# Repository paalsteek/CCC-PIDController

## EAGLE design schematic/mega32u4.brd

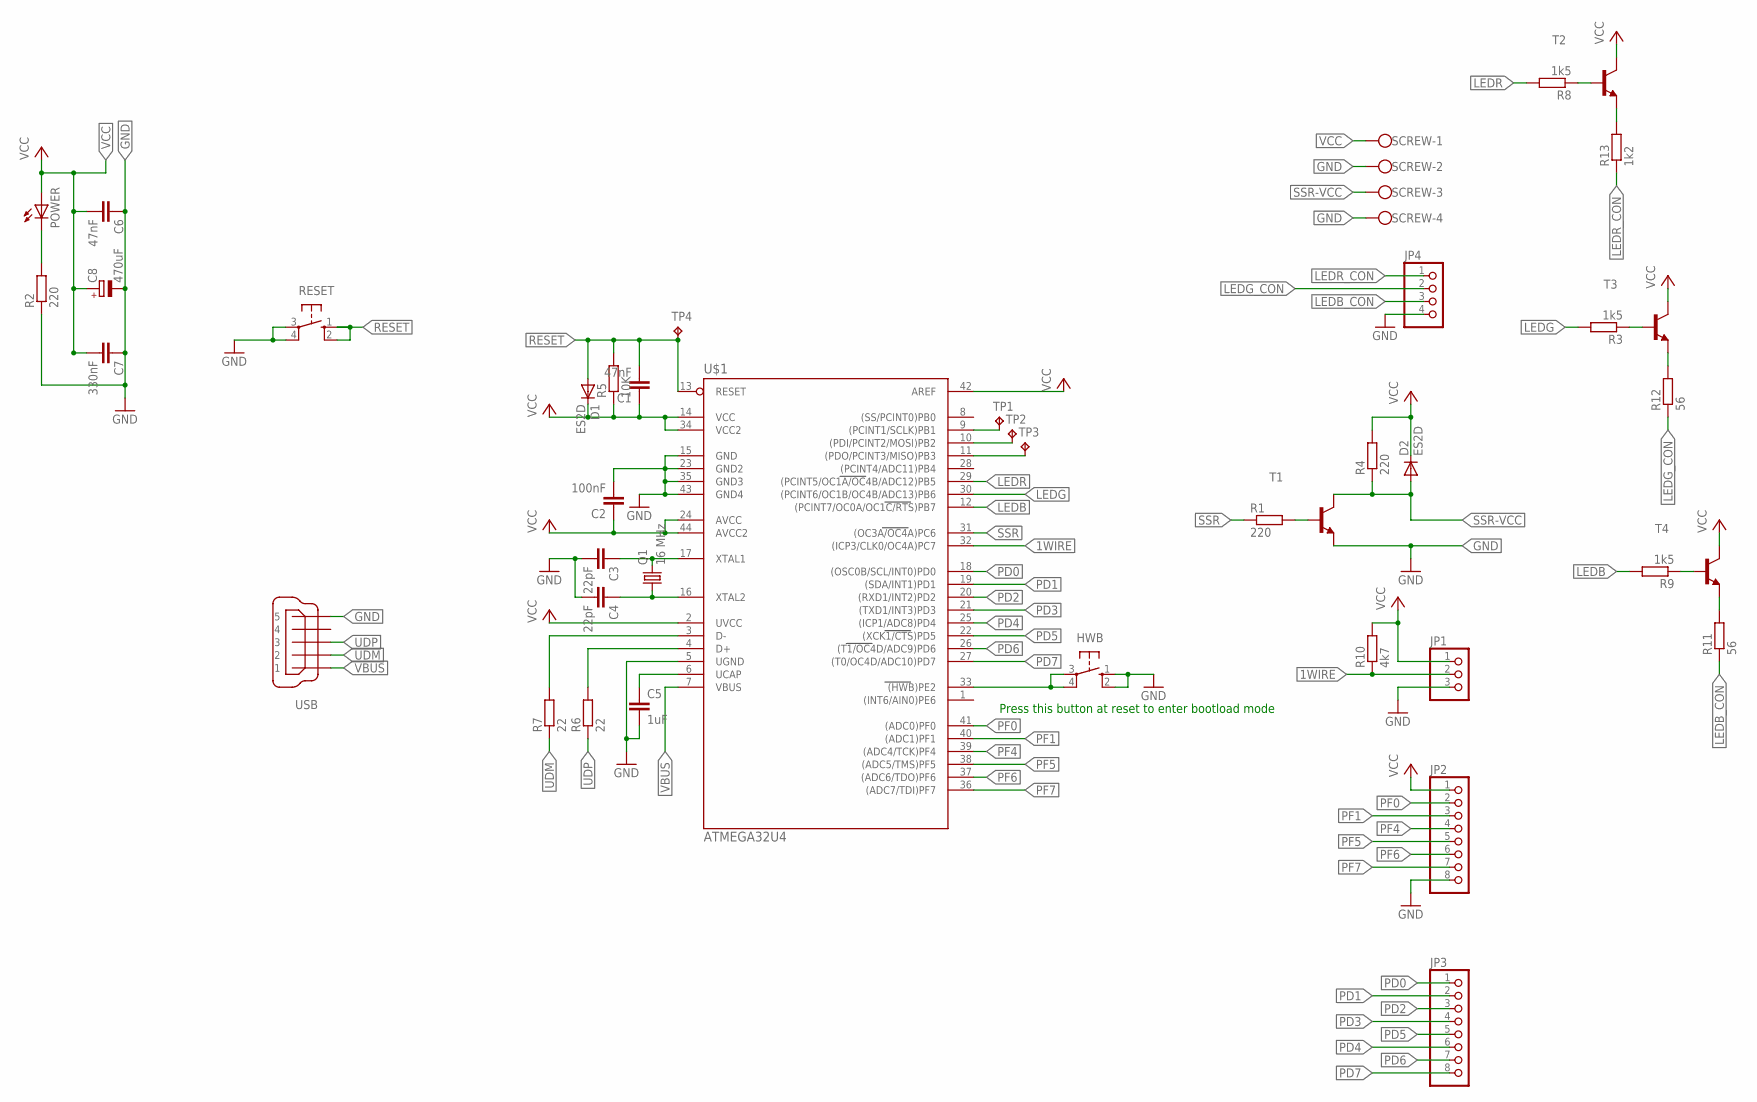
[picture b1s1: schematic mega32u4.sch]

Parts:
C1, C6: 47nF; C0805K
C2: 100nF; C0805K
C3, C4: 22pF; C0805K
C5: 1uF; C0805K
C7: 330nF; C0805K
C8: 470uF; 150CLZ-0810
D1, D2: ES2D; SMB
HWB: 10-XX; B3F-10XX
JP1: PINHD-1X3; 1X03
JP2, JP3: PINHD-1X8; 1X08
JP4: PINHD-1X4; 1X04
POWER: LEDSML0805; SML0805
Q1: 16 MHz; CTS406
R1, R2, R4: 220; R0805
R3, R8, R9: 1k5; R0805
R5: 10K; R0805
R6, R7: 22; R0805
R10: 4k7; R0805
R11, R12: 56; R0805
R13: 1k2; R0805
RESET: 10-XX; B3F-10XX; MPN B3F-1000
SCREW: W237-4
T1, T2, T3, T4: BC817-25-NPN-SOT23-BEC; SOT23-BEC
TP1, TP2, TP3, TP4: TPTP10R; TP10R
U$1: ATMEGA32U4; TQFP44
USB: MINI-USB-32005-201; 32005-201

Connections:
1WIRE: JP1.2, R10.1, U$1.32 ((ICP3/CLK0/OC4A)PC7)
GND: C2.2, C3.2, C4.2, C5.2, C6.1, C7.1, C8.-, HWB.1 (S), HWB.2 (S1), JP1.3, JP2.8, JP4.4, R2.1, RESET.3, RESET.4 (P1), SCREW.2, SCREW.4, T1.E, U$1.5 (UGND), U$1.15 (GND), U$1.23 (GND2), U$1.35 (GND3), U$1.43 (GND4), USB.5
LEDB: R9.2, U$1.12 ((PCINT7/OC0A/OC1C/RTS)PB7)
LEDB_CON: JP4.3, R11.1
LEDG: R3.2, U$1.30 ((PCINT6/OC1B/OC4B/ADC13)PB6)
LEDG_CON: JP4.2, R12.1
LEDR: R8.2, U$1.29 ((PCINT5/OC1A/OC4B/ADC12)PB5)
LEDR_CON: JP4.1, R13.1
unnamed: TP1.TP, U$1.9 ((PCINT1/SCLK)PB1)
unnamed: C3.1, Q1.3 (2), U$1.17 (XTAL1)
unnamed: C4.1, Q1.1, U$1.16 (XTAL2)
unnamed: C5.1, U$1.6 (UCAP)
unnamed: R1.2, T1.B
unnamed: R6.2, U$1.4 (D+)
unnamed: R7.2, U$1.3 (D-)
unnamed: R8.1, T2.B
unnamed: R3.1, T3.B
unnamed: HWB.3, HWB.4 (P1), U$1.33 ((HWB)PE2)
unnamed: R9.1, T4.B
unnamed: TP2.TP, U$1.10 ((PDI/PCINT2/MOSI)PB2)
unnamed: POWER.C, R2.2
unnamed: R11.2, T4.E
unnamed: R12.2, T3.E
unnamed: R13.2, T2.E
unnamed: TP3.TP, U$1.11 ((PDO/PCINT3/MISO)PB3)
PD0: JP3.1, U$1.18 ((OSC0B/SCL/INT0)PD0)
PD1: JP3.2, U$1.19 ((SDA/INT1)PD1)
PD2: JP3.3, U$1.20 ((RXD1/INT2)PD2)
PD3: JP3.4, U$1.21 ((TXD1/INT3)PD3)
PD4: JP3.6, U$1.25 ((ICP1/ADC8)PD4)
PD5: JP3.5, U$1.22 ((XCK1/CTS)PD5)
PD6: JP3.7, U$1.26 ((T1/OC4D/ADC9)PD6)
PD7: JP3.8, U$1.27 ((T0/OC4D/ADC10)PD7)
PF0: JP2.2, U$1.41 ((ADC0)PF0)
PF1: JP2.3, U$1.40 ((ADC1)PF1)
PF4: JP2.4, U$1.39 ((ADC4/TCK)PF4)
PF5: JP2.5, U$1.38 ((ADC5/TMS)PF5)
PF6: JP2.6, U$1.37 ((ADC6/TDO)PF6)
PF7: JP2.7, U$1.36 ((ADC7/TDI)PF7)
RESET: C1.2, D1.A, R5.2, RESET.1 (S), RESET.2 (S1), TP4.TP, U$1.13 (RESET)
SSR: R1.1, U$1.31 ((OC3A/OC4A)PC6)
SSR-VCC: D2.A, R4.1, SCREW.3, T1.C
UDM: R7.1, USB.2
UDP: R6.1, USB.3
VBUS: U$1.7 (VBUS), USB.1
VCC: C1.1, C2.1, C6.2, C7.2, C8.+, D1.C, D2.C, JP1.1, JP2.1, POWER.A, R4.2, R5.1, R10.2, SCREW.1, T2.C, T3.C, T4.C, U$1.2 (UVCC), U$1.14 (VCC), U$1.24 (AVCC), U$1.34 (VCC2), U$1.42 (AREF), U$1.44 (AVCC2)

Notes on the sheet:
Press this button at reset to enter bootload mode

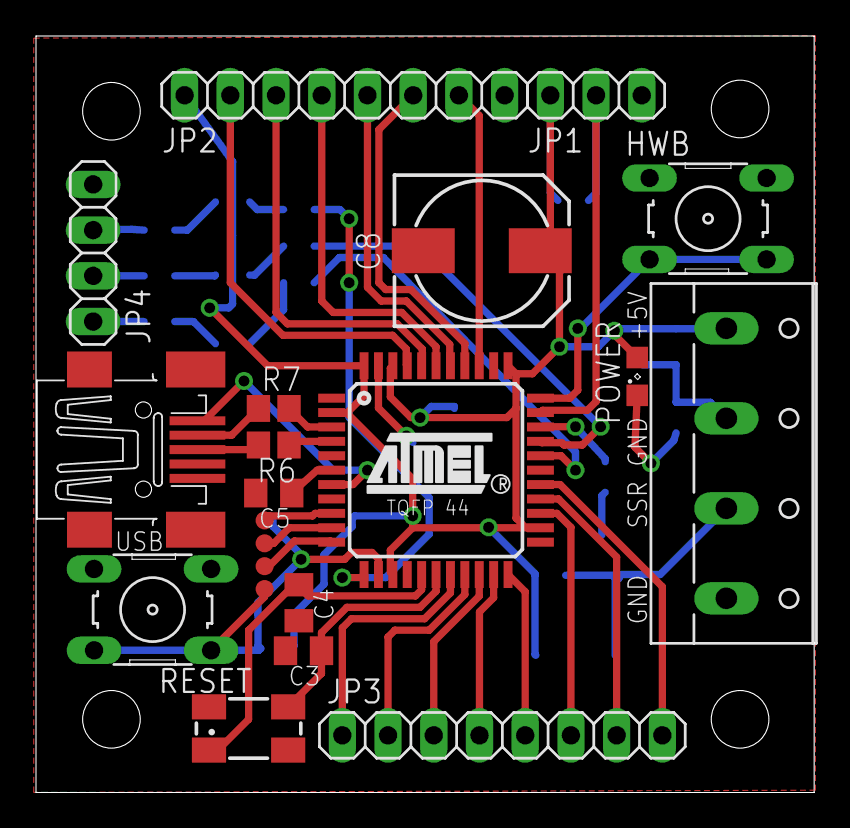
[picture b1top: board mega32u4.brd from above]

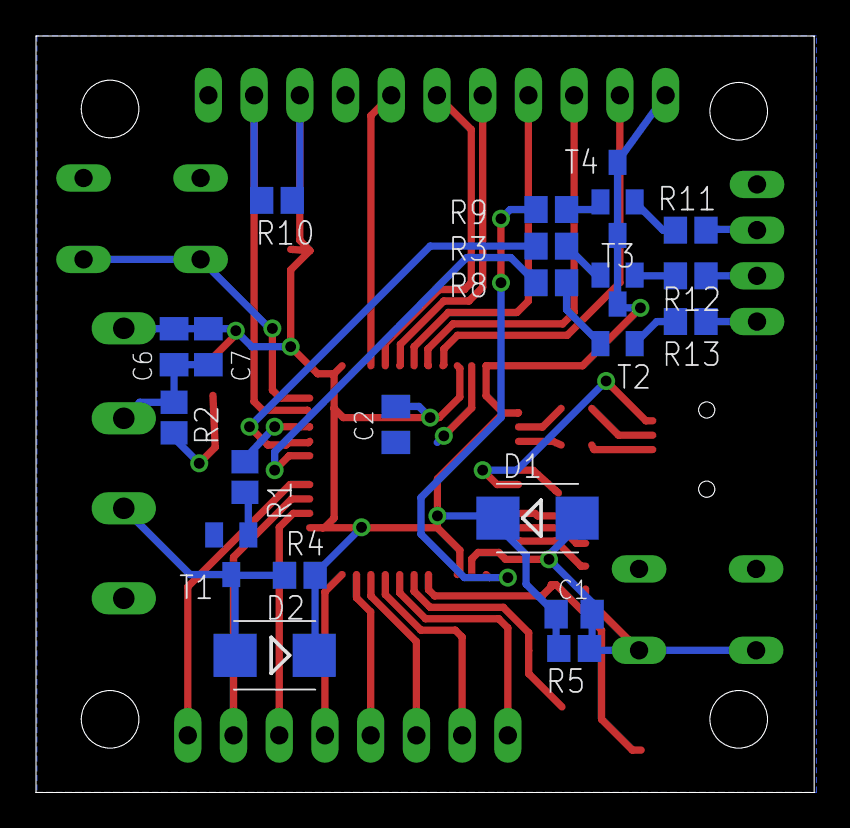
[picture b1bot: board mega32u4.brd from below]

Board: 2 copper layers, 43.2 x 42.0 mm, 42 parts (21 on the bottom side), 46 nets.

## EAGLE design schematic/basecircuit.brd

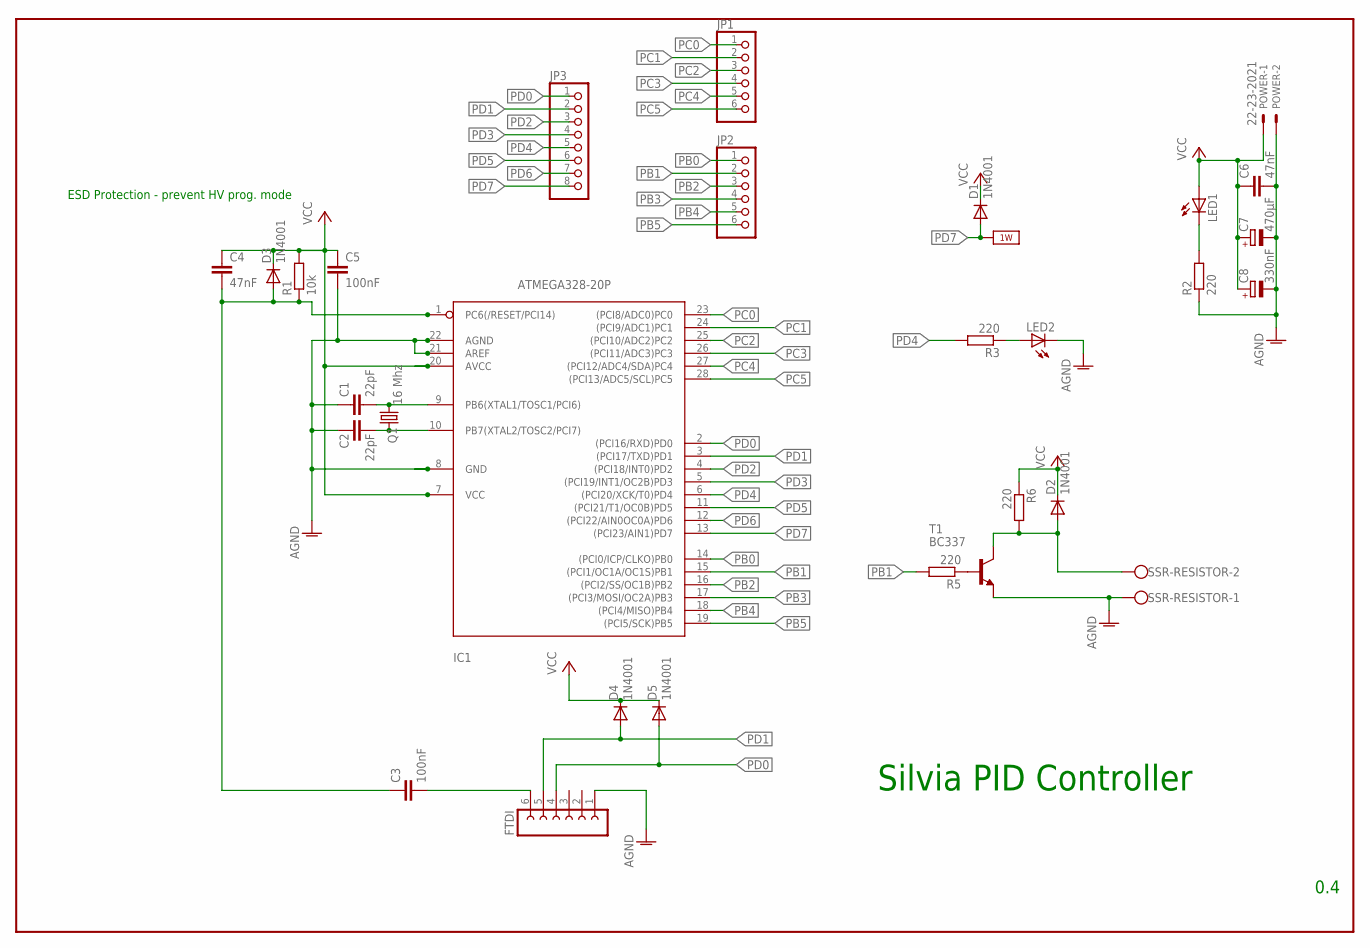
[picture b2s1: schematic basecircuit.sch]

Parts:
C1, C2: 22pF; C025-030X050
C3: 100nF; C025-030X050
C4, C6: 47nF; C025-030X050
C5: 100nF; C025-025X050
C7: 470µF; E2,5-6E
C8: 330nF; E2,5-6E
D1, D2, D3, D4, D5: 1N4001; DO41-10
FTDI: FE06-1; FE06
IC1: ATMEGA328-20P; DIL28-3
JP1, JP2: PINHD-1X6; 1X06
JP3: PINHD-1X8; 1X08
LED1, LED2: LED5MM
POWER: 22-23-2021
Q1: 16 Mhz; HC49U-V
R1: 10k; 0204/7
R2, R3, R5, R6: 220; 0204/7
SSR-RESISTOR: W237-102
T1: BC337; TO92

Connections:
AGND: C1.1, C2.1, C5.2, C6.2, C7.-, C8.-, FTDI.1, IC1.8 (GND), IC1.21 (AREF), IC1.22 (AGND), LED2.K (C), POWER.2, R2.1, SSR-RESISTOR.1, T1.1 (E)
unnamed: R5.1, T1.2 (B)
unnamed: LED1.K (C), R2.2
unnamed: C3.2, FTDI.6
unnamed: LED2.A, R3.1
unnamed: C1.2, IC1.9 (PB6(XTAL1/TOSC1/PCI6)), Q1.2
unnamed: C2.2, IC1.10 (PB7(XTAL2/TOSC2/PCI7)), Q1.1
unnamed: C3.1, C4.2, D3.A, IC1.1 (PC6(/RESET/PCI14)), R1.1
unnamed: D2.A, R6.2, SSR-RESISTOR.2, T1.3 (C)
PB0: IC1.14 ((PCI0/ICP/CLKO)PB0), JP2.1
PB1: IC1.15 ((PCI1/OC1A/OC1S)PB1), JP2.2, R5.2
PB2: IC1.16 ((PCI2/SS/OC1B)PB2), JP2.3
PB3: IC1.17 ((PCI3/MOSI/OC2A)PB3), JP2.4
PB4: IC1.18 ((PCI4/MISO)PB4), JP2.5
PB5: IC1.19 ((PCI5/SCK)PB5), JP2.6
PC0: IC1.23 ((PCI8/ADC0)PC0), JP1.1
PC1: IC1.24 ((PCI9/ADC1)PC1), JP1.2
PC2: IC1.25 ((PCI10/ADC2)PC2), JP1.3
PC3: IC1.26 ((PCI11/ADC3)PC3), JP1.4
PC4: IC1.27 ((PCI12/ADC4/SDA)PC4), JP1.5
PC5: IC1.28 ((PCI13/ADC5/SCL)PC5), JP1.6
PD0: D5.A, FTDI.4, IC1.2 ((PCI16/RXD)PD0), JP3.1
PD1: D4.A, FTDI.5, IC1.3 ((PCI17/TXD)PD1), JP3.2
PD2: IC1.4 ((PCI18/INT0)PD2), JP3.3
PD3: IC1.5 ((PCI19/INT1/OC2B)PD3), JP3.4
PD4: IC1.6 ((PCI20/XCK/T0)PD4), JP3.5, R3.2
PD5: IC1.11 ((PCI21/T1/OC0B)PD5), JP3.6
PD6: IC1.12 ((PCI22/AIN0OC0A)PD6), JP3.7
PD7: D1.A, IC1.13 ((PCI23/AIN1)PD7), JP3.8
VCC: C4.1, C5.1, C6.1, C7.+, C8.+, D1.C, D2.C, D3.C, D4.C, D5.C, IC1.7 (VCC), IC1.20 (AVCC), LED1.A, POWER.1, R1.2, R6.1

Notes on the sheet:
0.4
Silvia PID Controller
ESD Protection - prevent HV prog. mode

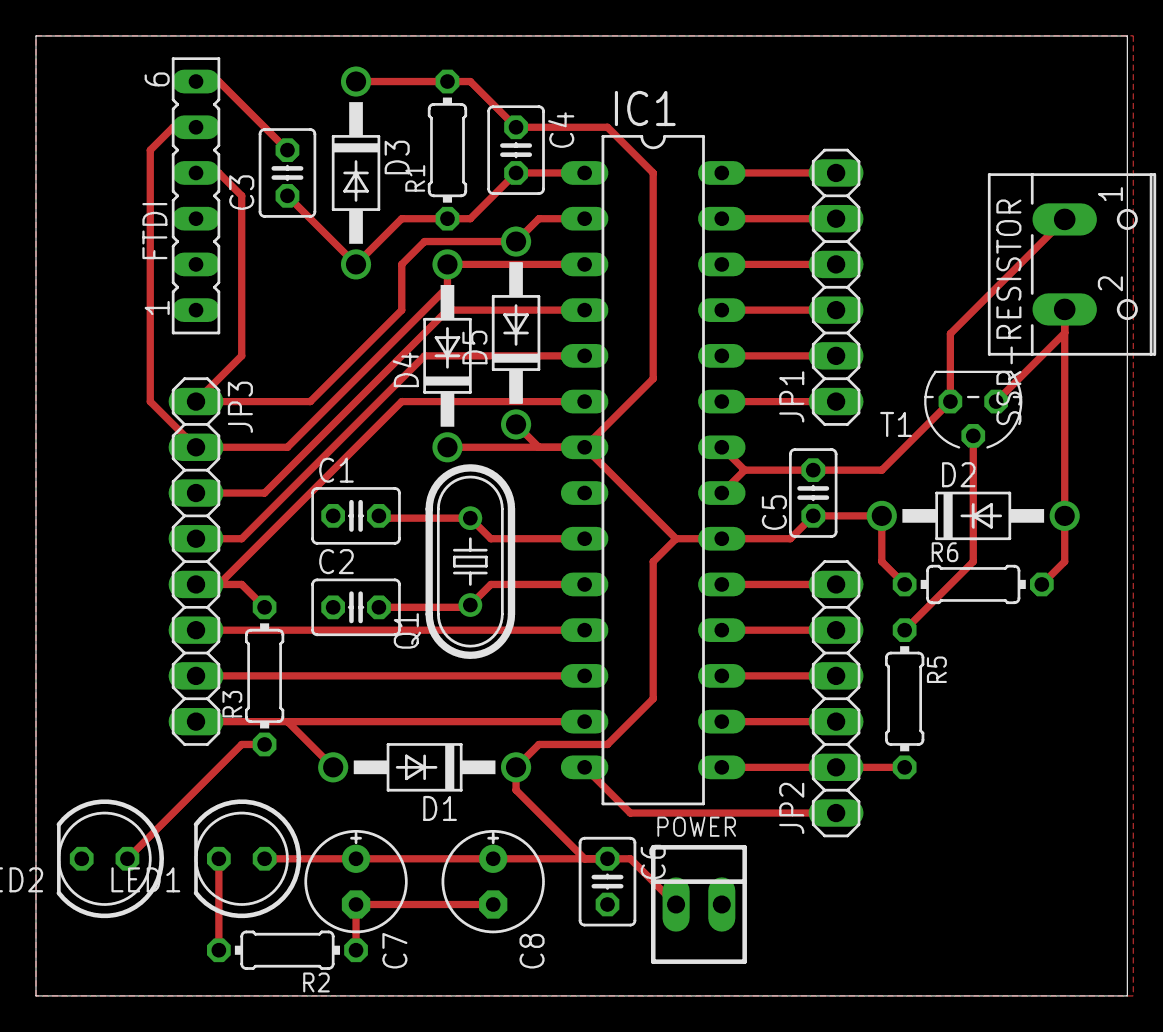
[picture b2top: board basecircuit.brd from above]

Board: 2 copper layers, 60.6 x 53.3 mm, 29 parts (0 on the bottom side), 30 nets.

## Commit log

2012-05-06 first layout
2012-05-07 some optimization
2012-05-10 new board based on an ATmega32u4
2012-05-10 Design Rule Check applied and errors corrected
2012-05-26 RGB-Led added, pin header repositioned, mounting holes added, ...
2012-05-26 Labels modified
2012-05-30 minor changes
2012-07-27 bug fixes
2012-09-22 [firmware] start of new firmware based on the LUFA library
2012-09-23 tempsensors added and uart replaced by virtual serial
2012-09-23 [firmware] pidcontroller added
2014-02-27 firmware ported to use the virtual serial of lufa
